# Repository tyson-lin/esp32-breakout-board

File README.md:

Design files for a custom ESP32 breakout board that includes an on-board battery management unit.

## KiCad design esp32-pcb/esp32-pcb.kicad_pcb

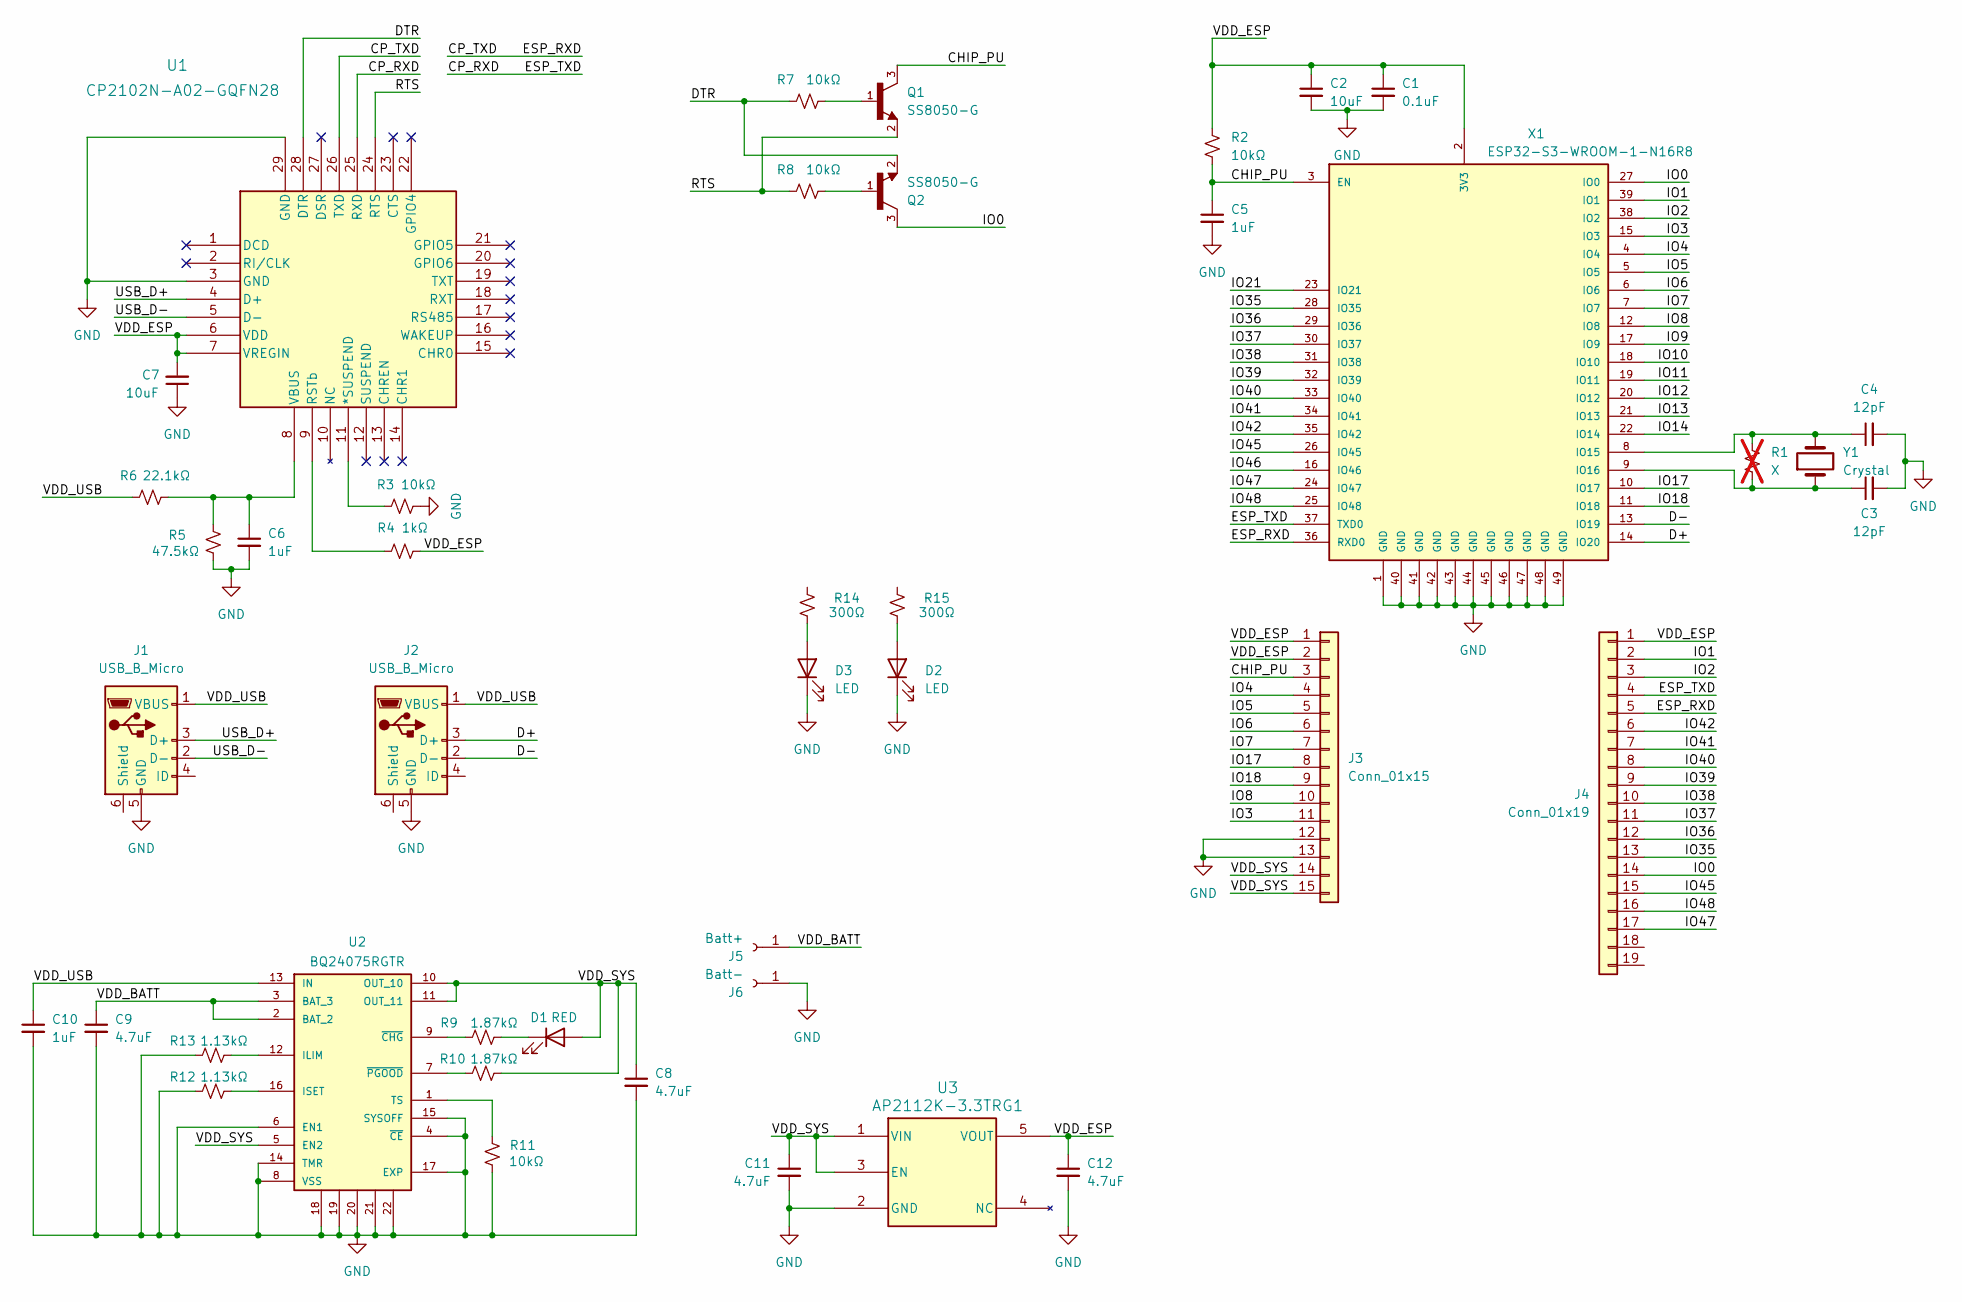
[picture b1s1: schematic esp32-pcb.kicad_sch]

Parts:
C1: 0.1uF; C_0402_1005Metric_Pad0.74x0.62mm_HandSolder; Rating 50V; Tolerance 10%
C2, C7: 10uF; C_0402_1005Metric_Pad0.74x0.62mm_HandSolder; Rating 25V; Tolerance 20%
C3, C4: 12pF; C_0402_1005Metric_Pad0.74x0.62mm_HandSolder
C5, C6, C10: 1uF; C_0402_1005Metric_Pad0.74x0.62mm_HandSolder; Rating 16V; Tolerance 10%
C8, C9, C11, C12: 4.7uF; C_0402_1005Metric_Pad0.74x0.62mm_HandSolder; Rating 16V; Tolerance 10%
D1: RED; LED_0603_1608Metric_Pad1.05x0.95mm_HandSolder
D2, D3: LED; D_0603_1608Metric_Pad1.05x0.95mm_HandSolder
J1, J2: USB_B_Micro; CUI_UJ2-MIBH2-4-SMT
J3: Conn_01x15; PinHeader_1x15_P2.54mm_Vertical
J4: Conn_01x19; PinHeader_1x19_P2.54mm_Vertical
J5: Batt+; PinHeader_1x01_P2.54mm_Vertical
J6: Batt-; PinHeader_1x01_P2.54mm_Vertical
Q1, Q2: SS8050-G; TRANS_SS8050-G; PARTREV A
R1: X; R_0402_1005Metric_Pad0.72x0.64mm_HandSolder; not fitted
R2, R3, R7, R8, R11: 10kΩ; R_0402_1005Metric_Pad0.72x0.64mm_HandSolder; Tolerance 1%
R4: 1kΩ; R_0402_1005Metric_Pad0.72x0.64mm_HandSolder; Tolerance 1%
R5: 47.5kΩ; R_0402_1005Metric_Pad0.72x0.64mm_HandSolder; Tolerance 1%
R6: 22.1kΩ; R_0402_1005Metric_Pad0.72x0.64mm_HandSolder; Tolerance 1%
R9, R10: 1.87kΩ; R_0402_1005Metric_Pad0.72x0.64mm_HandSolder; Tolerance 1%
R12, R13: 1.13kΩ; R_0402_1005Metric_Pad0.72x0.64mm_HandSolder; Tolerance 1%
R14, R15: 300Ω; R_0402_1005Metric_Pad0.72x0.64mm_HandSolder; Tolerance 1%
U1: CP2102N-A02-GQFN28; QFN28_5X5_SIL
U2: BQ24075RGTR; QFN50P300X300X100-17N; PARTREV M
U3: AP2112K-3.3TRG1; SOT_RG1_DIO
X1: ESP32-S3-WROOM-1-N16R8; ESP32S3WROOM1N8R2; MANUFACTURER_PART_NUMBER ESP32-S3-WROOM-1-N16R8
Y1: Crystal; 12.87159_GYE

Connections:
/CHIP_PU: C5.1, J3.3, Q1.3, R2.1, X1.3 (EN)
/CP_RXD: J4.4, U1.25 (RXD), X1.37 (TXD0)
/CP_TXD: J4.5, U1.26 (TXD), X1.36 (RXD0)
/D+: J2.3 (D+), X1.14 (IO20)
/D-: J2.2 (D-), X1.13 (IO19)
/DTR: Q2.2, R7.2, U1.28 (DTR)
/IO0: J4.14, Q2.3, X1.27 (IO0)
/IO1: J4.2, X1.39 (IO1)
/IO2: J4.3, X1.38 (IO2)
/IO3: J3.11, X1.15 (IO3)
/IO4: J3.4, X1.4 (IO4)
/IO5: J3.5, X1.5 (IO5)
/IO6: J3.6, X1.6 (IO6)
/IO7: J3.7, X1.7 (IO7)
/IO8: J3.10, X1.12 (IO8)
/IO9: X1.17 (IO9)
/IO10: X1.18 (IO10)
/IO11: X1.19 (IO11)
/IO12: X1.20 (IO12)
/IO13: X1.21 (IO13)
/IO14: X1.22 (IO14)
/IO17: J3.8, X1.10 (IO17)
/IO18: J3.9, X1.11 (IO18)
/IO21: X1.23 (IO21)
/IO35: J4.13, X1.28 (IO35)
/IO36: J4.12, X1.29 (IO36)
/IO37: J4.11, X1.30 (IO37)
/IO38: J4.10, X1.31 (IO38)
/IO39: J4.9, X1.32 (IO39)
/IO40: J4.8, X1.33 (IO40)
/IO41: J4.7, X1.34 (IO41)
/IO42: J4.6, X1.35 (IO42)
/IO45: J4.15, X1.26 (IO45)
/IO46: X1.16 (IO46)
/IO47: J4.17, X1.24 (IO47)
/IO48: J4.16, X1.25 (IO48)
/RTS: Q1.2, R8.2, U1.24 (RTS)
/USB_D+: J1.3 (D+), U1.4 (D+)
/USB_D-: J1.2 (D-), U1.5 (D-)
/VDD_BATT: C9.1, J5.1, U2.2 (BAT_2), U2.3 (BAT_3)
/VDD_ESP: C1.1, C2.1, C7.2, C12.1, J3.1, J3.2, J4.1, R2.2, R4.1, U1.6 (VDD), U1.7 (VREGIN), U3.5 (VOUT), X1.2 (3V3)
/VDD_SYS: C8.1, C11.1, D1.2 (A), J3.14, J3.15, R10.2, U2.5 (EN2), U2.10 (OUT_10), U2.11 (OUT_11), U3.1 (VIN), U3.3 (EN)
/VDD_USB: C10.1, J1.1 (VBUS), J2.1 (VBUS), R6.2, U2.13 (IN)
GND: C1.2, C2.2, C3.2, C4.2, C5.2, C6.2, C7.1, C8.2, C9.2, C10.2, C11.2, C12.2, D2.1 (K), D3.1 (K), J1.5 (GND), J2.5 (GND), J3.12, J3.13, J6.1, R3.1, R5.2, R11.1, R12.1, R13.1, U1.3 (GND), U1.29 (GND), U2.4 (~CE), U2.6 (EN1), U2.8 (VSS), U2.14 (TMR), U2.15 (SYSOFF), U2.17 (EXP), U2.18, U2.19, U2.20, U2.21, U2.22, U3.2 (GND), X1.1 (GND), X1.40 (GND), X1.41 (GND), X1.42 (GND), X1.43 (GND), X1.44 (GND), X1.45 (GND), X1.46 (GND), X1.47 (GND), X1.48 (GND), X1.49 (GND)
unnamed: D1.1 (K), R9.2
unnamed: D2.2 (A), R15.1
unnamed: D3.2 (A), R14.1
unnamed: Q1.1, R7.1
unnamed: Q2.1, R8.1
unnamed: R3.2, U1.11 (*SUSPEND)
unnamed: R4.2, U1.9 (RSTb)
unnamed: C6.1, R5.1, R6.1, U1.8 (VBUS)
unnamed: R13.2, U2.12 (ILIM)
unnamed: R12.2, U2.16 (ISET)
unnamed: R11.2, U2.1 (TS)
unnamed: R9.1, U2.9 (~CHG)
unnamed: R10.1, U2.7 (~PGOOD)
unnamed: C4.1, R1.1, X1.8 (IO15), Y1.2
unnamed: C3.1, R1.2, X1.9 (IO16), Y1.1

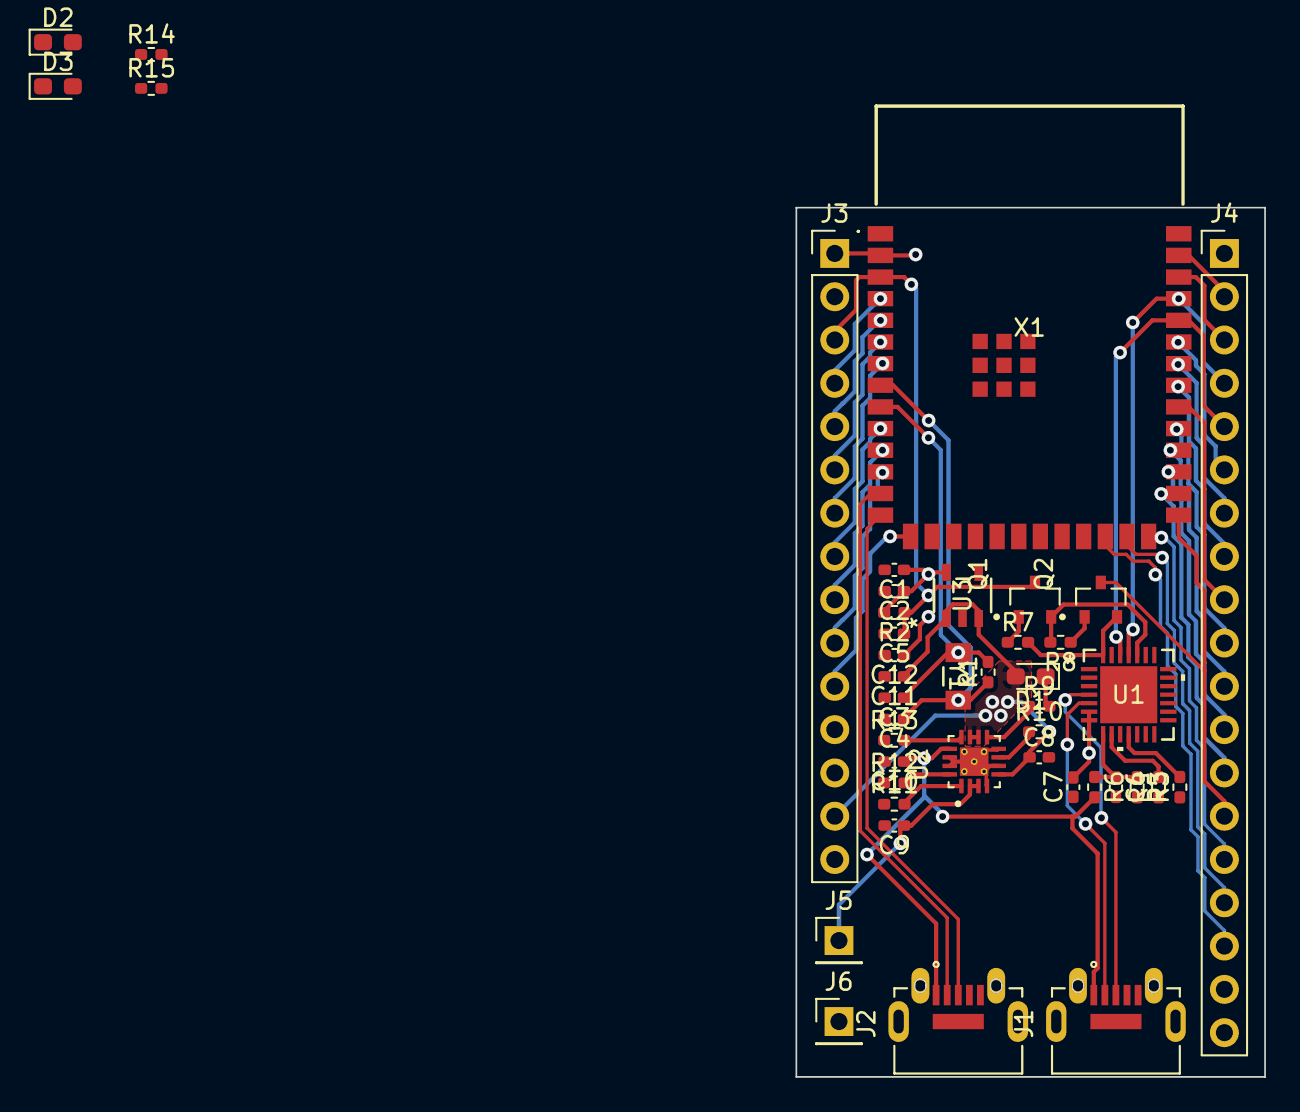
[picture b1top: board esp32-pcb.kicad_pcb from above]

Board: 2 copper layers, 27.5 x 51.0 mm, 43 parts (0 on the bottom side), 51 nets.

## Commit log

2024-12-22 Adding .gitignore
2025-05-21 updates from work
